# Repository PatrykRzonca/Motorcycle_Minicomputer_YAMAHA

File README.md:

# Motorcycle_Minicomputer_YAMAHA
Mini computer for motorcycle

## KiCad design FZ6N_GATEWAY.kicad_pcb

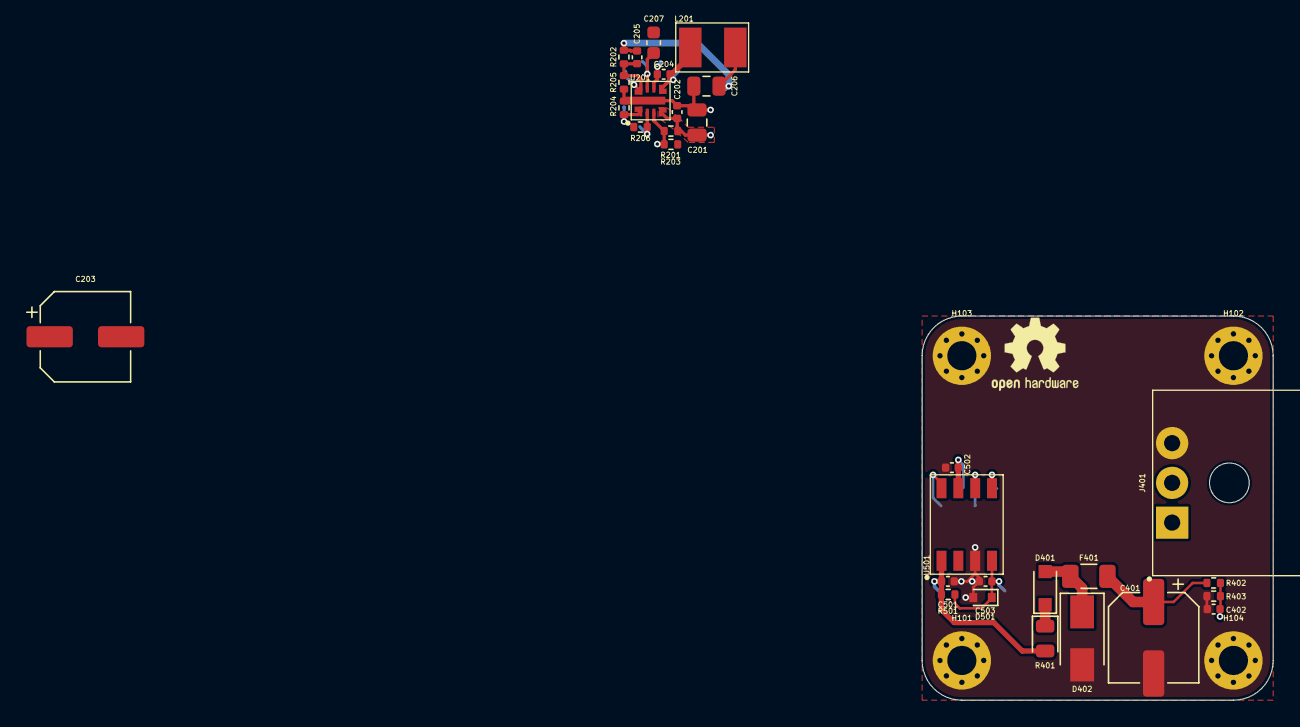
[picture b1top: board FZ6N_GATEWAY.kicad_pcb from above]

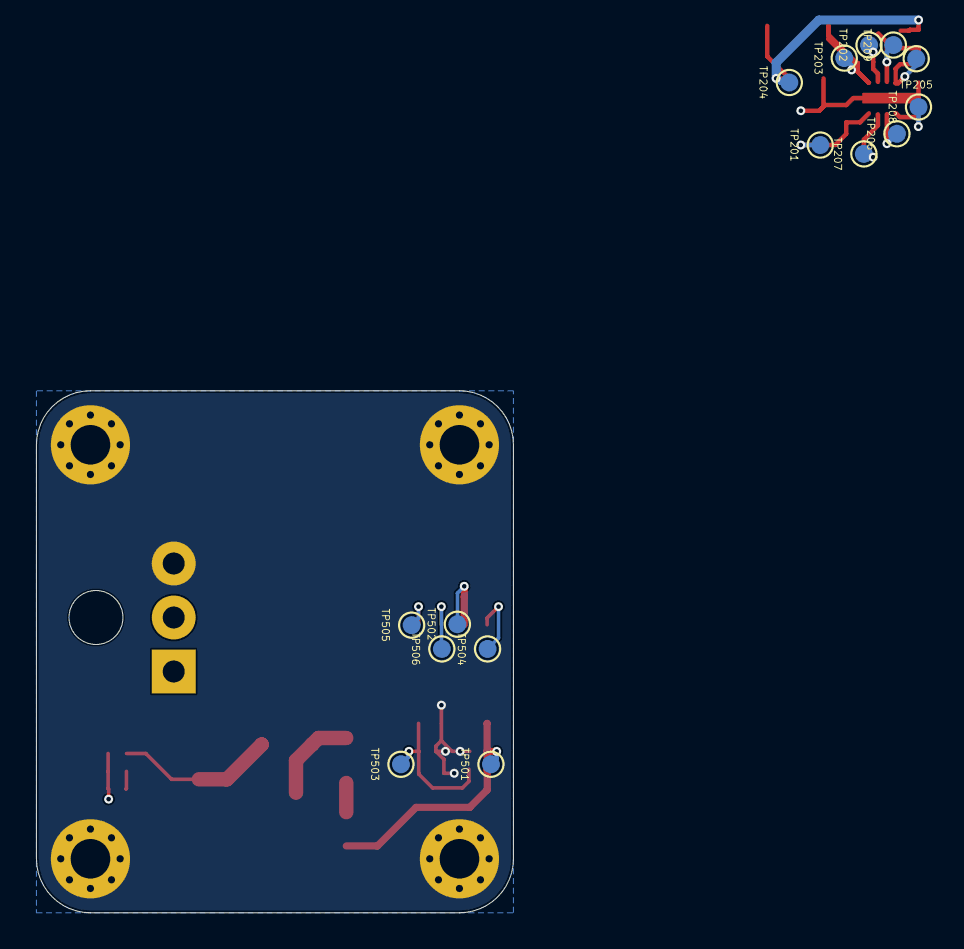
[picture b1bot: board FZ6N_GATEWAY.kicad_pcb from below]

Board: 4 copper layers, 26.5 x 29.0 mm, 50 parts (15 on the bottom side), 18 nets.

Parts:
C201: 2u2; C_0805_2012Metric
C202, C204, C402: 100n; C_0402_1005Metric
C203: 4u7; CP_Elec_6.3x7.7
C205, C501, C502, C503: 10n; C_0402_1005Metric
C206: 22u; C_0805_2012Metric
C207: 1u; C_0603_1608Metric
C401: 22u; CP_Elec_6.3x5.7
D401: 350mV; D_SOD-323_HandSoldering
D402: 22V; D_SMA
D501: 24V; D_SOD-523
F401: Fuse; Fuse_1206_3216Metric
H101, H102, H103, H104: MountingHole_Pad; MountingHole_2.2mm_M2_Pad_Via
J401: Conn_01x03_Male; 2-1445055-3
L201: 82u; PM1812-820J-RC
N101: Housing; OSHW-Logo2_7.3x6mm_SilkScreen
R201: 340k; R_0402_1005Metric
R202: 100k; R_0402_1005Metric
R203, R204, R403: 15k8; R_0402_1005Metric
R205: 43k2; R_0402_1005Metric
R206: 4k7; R_0402_1005Metric
R401: 340k; D_0805_2012Metric
R402: 71k5; R_0402_1005Metric
R501: 510R; R_0402_1005Metric
TP201, TP202, TP203, TP204, TP205, TP206, TP207, TP208, TP209, TP501, TP502, TP503, TP504, TP505, TP506: TestPoint; TestPoint_Pad_D1.0mm
U201: LMR36503; LMR36503_VQFN-HR-9
U501: MC33660; MC33660_SOICN-8

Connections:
+3V3: C205.2, C206.2, C502.2, L201.2, R202.2, R206.2, TP204.1, TP502.1, U501.7
+12P: C201.2, C202.2, C501.2, R201.2, R401.2, R501.2, TP201.1, TP501.1, U201.4, U501.1
+12V: C401.1, F401.2, J401.1, R402.2
/LMR36503/BOOT: C204.2, TP202.1, U201.6
/LMR36503/EN: R201.1, R203.2, TP207.1, U201.3
/LMR36503/FB: C205.1, R202.1, R205.2, TP205.1, U201.8
/LMR36503/PGOOD: R206.1, TP206.1, U201.2
/LMR36503/RT: R204.2, TP208.1, U201.1
/LMR36503/SW: C204.1, L201.1, TP203.1, U201.5
/LMR36503/VCC: C207.2, TP209.1, U201.7
/MC33660/ISO_CEN: TP504.1, U501.8
/MC33660/ISO_KLINE: C503.2, D501.1, R501.1, TP503.1, U501.4
/MC33660/ISO_RX: TP506.1, U501.6
/MC33660/ISO_TX: TP505.1, U501.5
/POWER/FUSE/MEASURE/VBAT_ADC: C402.2, R402.1, R403.2
GND: C201.1, C202.1, C203.1, C203.2, C206.1, C207.1, C401.2, C402.1, C501.1, C502.1, C503.1, D402.2, D501.2, H101.1, H102.1, H103.1, H104.1, J401.3, R203.1, R204.1, R205.1, R403.1, U201.9, U501.3
unnamed: D401.1, R401.1
unnamed: D401.2, D402.1, F401.1

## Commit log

2022-03-30 First release
